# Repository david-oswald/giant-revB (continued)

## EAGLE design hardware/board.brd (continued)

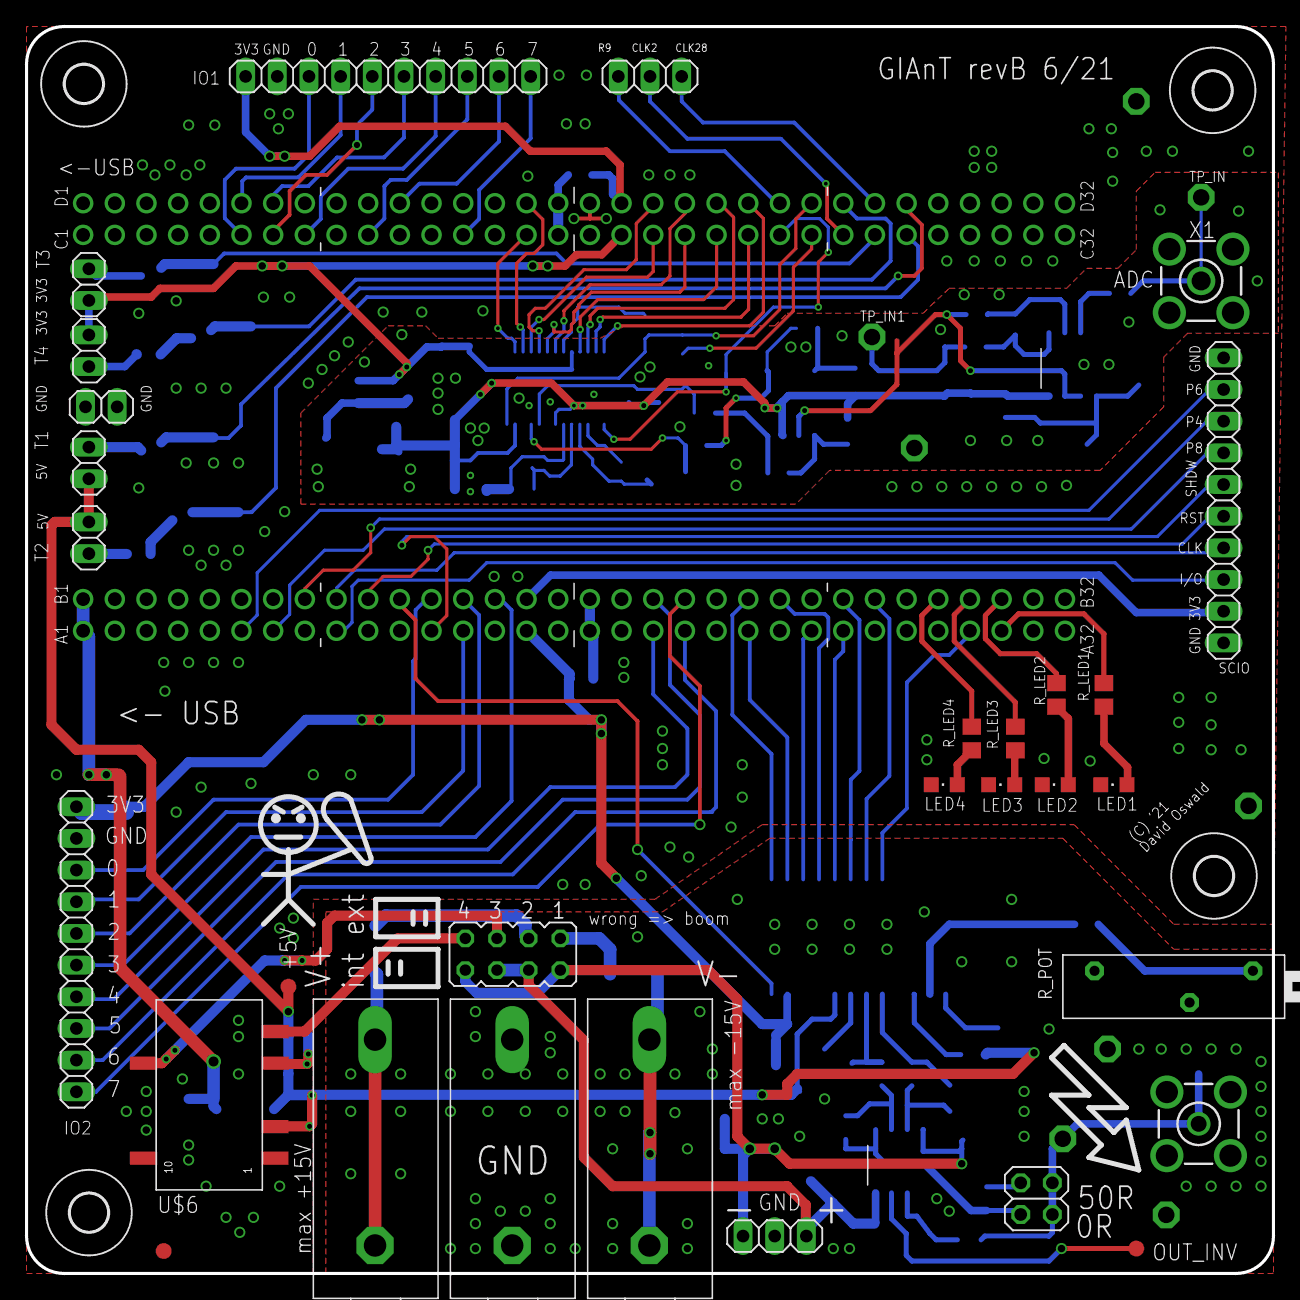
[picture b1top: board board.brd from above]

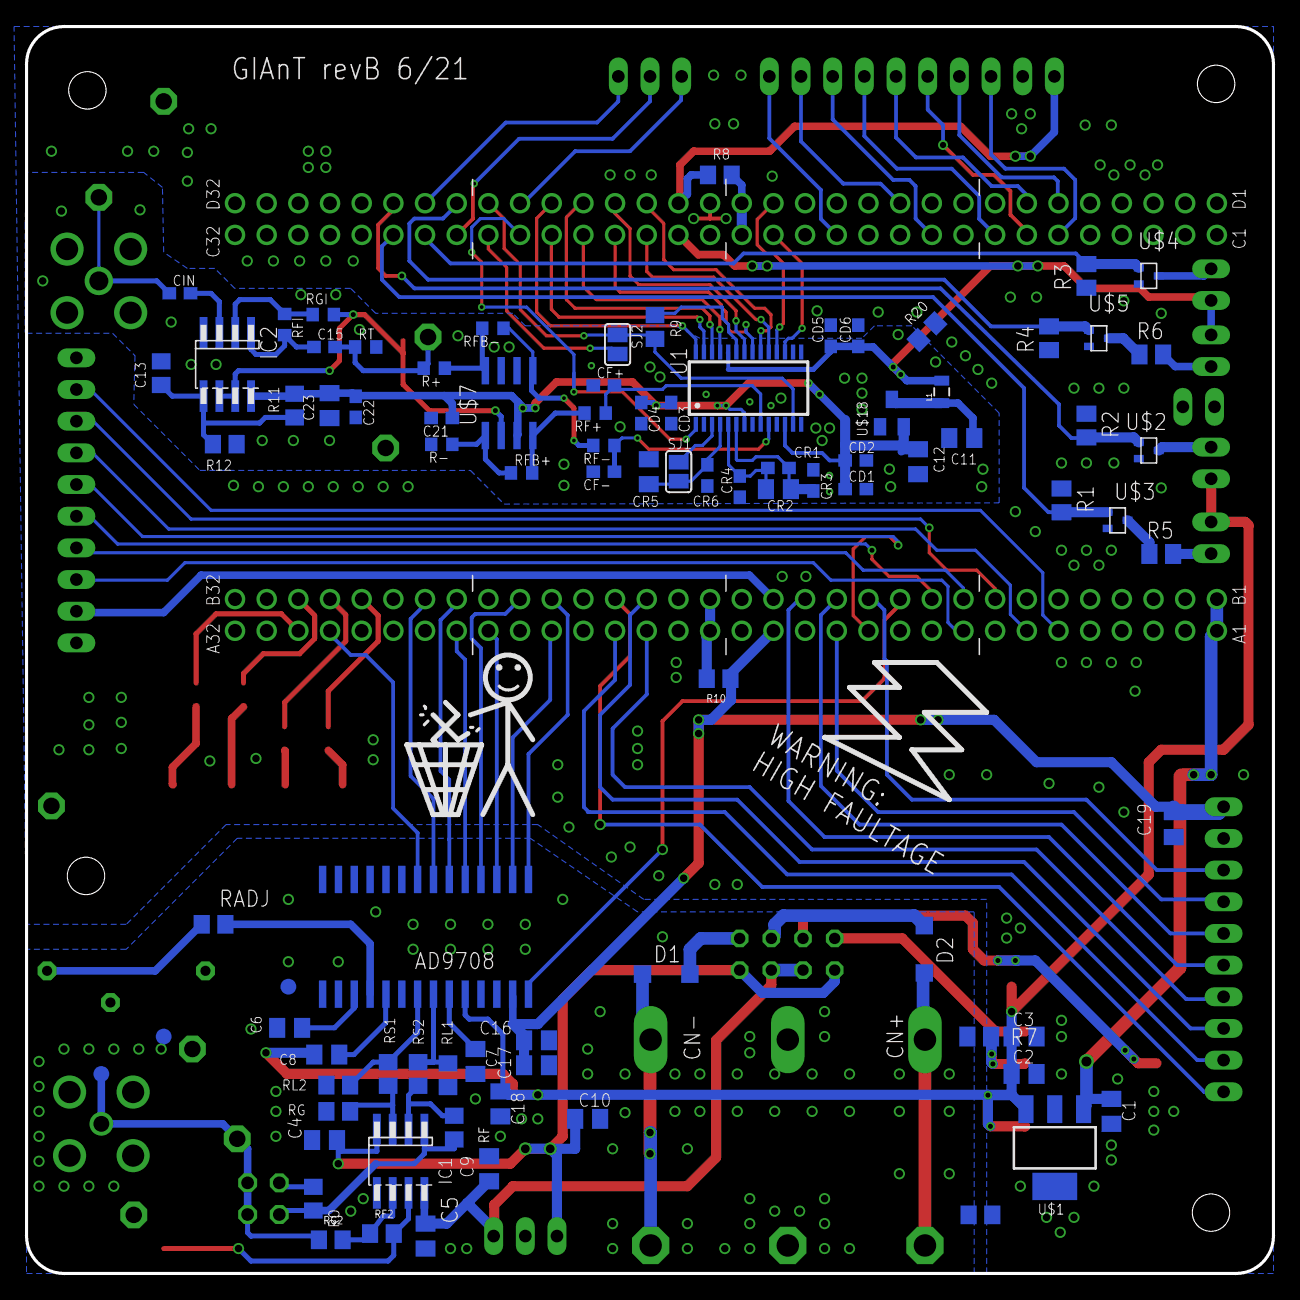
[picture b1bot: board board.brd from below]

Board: 2 copper layers, 100.0 x 100.0 mm, 131 parts (88 on the bottom side), 119 nets.

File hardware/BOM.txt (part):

Qty Value            Device                Package           Parts                                                        Description                            
1                    BU-SMA-V              BU-SMA-V          DAC_OUT                                                      FEMALE SMA CONNECTOR                                      
2                    DIODE-SOD123          SOD123            D1, D2                                                       DIODE                                                                            
4                    DMG1012UW             DMG1012UW1-SMT323 U$2, U$3, U$4, U$5                                           NPN DMG1012UW                                                                    
1                    JP4Q                  JP4Q              JP1                                                          JUMPER                                                                           
4                    LEDCHIPLED_0805       CHIPLED_0805      LED1, LED2, LED3, LED4                                       LED                                                                              
3                    PINHD-1X10            1X10              GPIO, GPIO2, SCIO                                            PIN HEADER                                                                       
5                    PINHD-1X2             1X02              JP2, JP3, JP4, JP5, JP6                                      PIN HEADER                                                                       
2                    PINHD-1X3             1X03              JP7, OP_VCC                                                  PIN HEADER                                                                       
1                    PINHD-2X2             2X02              DAC_T                                                        PIN HEADER                                                                       
4   tbd 	         R-EU_R0805            R0805             R_LED1, R_LED2, R_LED3, R_LED4                               RESISTOR, European symbol                                                        
4   0                R-EU_R0805            R0805             R8, R10, R20, R_GND1                                         RESISTOR, European symbol                                                        
7   0.1u             C-EUC0805K            C0805K            C4, C5, C6, C7, C8, C16, C18                                 CAPACITOR, European symbol                                                       
1   0R               R-EU_M0805            M0805             R7                                                           RESISTOR, European symbol                                                        
2   0R               SJ                    SJ                SJ1, SJ2                                                     SMD solder JUMPER                                                                
1   1.9k             R-EU_R0805            R0805             RADJ                                                         RESISTOR, European symbol                                                        
4   100k             R-EU_M0805            M0805             R1, R2, R3, R4                                               RESISTOR, European symbol                                                        
11  100n             C-EUC0603             C0603             C15, C21, C22, CD1, CD3, CD6, CIN, CR1, CR3, CR4, CR6        CAPACITOR, European symbol                                                       
1   100n             C-EUC0805             C0805             C13                                                          CAPACITOR, European symbol                                                       
1   100n             C-EUC0805K            C0805K            C1                                                           CAPACITOR, European symbol                                                       
1   10k              POTENTIOMETER_PT_SPIN PT-SPIN           R_POT                                                        Potentiometer                                                                    
2   10k              R-EU_R0805            R0805             R11, R12                                                     RESISTOR, European symbol                                                        
3   10n              C-EUC0603             C0603             CD2, CD4, CD5                                                CAPACITOR, European symbol                                                       
1   10n              C-EUC0805K            C0805K            C19                                                          CAPACITOR, European symbol                                                       
5   10u              C-EUC0805K            C0805K            C2, C3, C9, C10, C17                                         CAPACITOR, European symbol                                                       
2   10µ              C-EUC0805K            C0805K            CR2, CR5                                                     CAPACITOR, European symbol                                                       
1   120n, footprint? INDUCTOR0805          0805              L1                                                           Inductors                                                                        
2   1k               R-EU_R0603            R0603             RFB+, RFB-                                                   RESISTOR, European symbol                                                        
2   1µ               C-EUC0805K            C0805K            C11, C12                                                     CAPACITOR, European symbol                                                       
2   20k              R-EU_R0603            R0603             RFI, RGI                                                     RESISTOR, European symbol                                                        
3   24243            24243                 24_243            CN+, CN-, CNG                                                Multicomp 24.243 Series                                                          
1   4.7µ             C-EUC0805K            C0805K            C23                                                          CAPACITOR, European symbol                                                       
3   49               R-EU_R0603            R0603             RF+, RF-, RT                                                 RESISTOR, European symbol                                                        
1   499              R-EU_R0603            R0603             R+                                                           RESISTOR, European symbol                                                        
1   50               R-EU_R0805            R0805             RO                                                           RESISTOR, European symbol                                                        
1   523              R-EU_R0603            R0603             R-                                                           RESISTOR, European symbol                                                        
4   68               R-EU_R0805            R0805             RL1, RL2, RS1, RS2                                           RESISTOR, European symbol                                                        
4   680              R-EU_R0805            R0805             RF, RF2, RG, RG2                                             RESISTOR, European symbol                                                        
1   AD7908           AD7908                SO28W             AD9708                                                       AD9708 8-Bit DAC with current output                                             
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
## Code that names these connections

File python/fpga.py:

# This file contains register definitions and constants for the FPGA
from enum import Enum


class Commands(Enum):
    FPGA_READ_REGISTER = 0x01
    FPGA_WRITE_REGISTER = 0x02
    FPGA_RESET = 0x03

class Registers(Enum):

    ## Read-only registers
    
    # Smartcard
    SC_STATUS = 3
    SC_DATA_OUT = 4
    SC_DATA_OUT_COUNT = 9
    SC_DATA_IN_COUNT = 10

    # PIC programmer
    PIC_DATA_OUT_L = 5
    PIC_DATA_OUT_H = 6
    
    # FI pulse generator
    FI_STATUS = 7
    FI_DATA_OUT = 8
    
    # DDR (currently disabled)
    DDR_DMA_IN_L = 11
    DDR_SINGLE_READ = 17
    DDR_STATUS = 18
    DDR_DMA_IN_H = 19
    
    # Threshold trigger (currently disabled)
    THRESHOLD_STATUS = 12
    
    # Utiming
    UTIMING_STATUS = 13
    
    # UTX
    UTX_PACKET_COUNT = 14
    UTX_STATUS = 22
    
    # URX
    URX_STATUS = 23       
    URX_DATA_OUT = 24  
    URX_PACKET_SIZE_OUT_LOW = 25 
    URX_PACKET_COUNT = 26
    URX_PACKET_SIZE_OUT_HIGH = 29
    
    # Utrig
    UTRIG1_STATUS = 27
    UTRIG2_STATUS = 28
    
    ## Read-write registers
    
    # Smartcard
    SC_CONTROL = 34
    SC_DATA_IN = 35
    
    PIC_CONTROL = 36
    PIC_COMMAND = 37
    PIC_DATA_IN_L = 38
    PIC_DATA_IN_H = 39
    
    # DAC
    DAC_V_LOW = 40
    DAC_V_HIGH = 41
    DAC_V_OFF = 46
    DAC_CONTROL = 48

    # FI pulse generator
    FI_CONTROL = 42
    FI_DATA_IN = 43
    FI_ADDR_L = 44
    FI_ADDR_H = 45
    FI_TRIGGER_CONTROL = 47
    FI_UNIVERSAL_TRIGGER_CONTROL = 81
   
    # Threshold trigger (currently disabled)
    THRESHOLD_CONTROL = 49
    THRESHOLD_VALUE = 61
    
    # Utiming
    UTIMING_CONTROL = 50
    UTIMING_DATA_IN = 51
    UTIMING_ADDR_L = 52
    UTIMING_ADDR_H = 53
    
    # RFID (currently disabled)
    RFID_RESET_TIME = 54
    RFID_CONTROL = 55
    
    # DDR (currently disabled)
    DDR_CONTROL = 56
    DDR_SINGLE_WRITE = 57
    DDR_ADDRESS = 58
    DDR_DATA_COUNT = 59
    
    # Pattern trigger (currently disabled)
    DETECTOR_PATTERN = 60
    DETECTOR_DEBUG = 62
    DETECTOR_PATTERN_SAMPLE_COUNT = 63
    
    # ADC (currently disabled)
    ADC_CONTROL = 64
    
    # Downsampling (currently disabled)
    SCOPE_DOWNSAMPLING_FACTOR = 65
    DETECTOR_DOWNSAMPLING_FACTOR = 66
    
    # UTX
    UTX_CONTROL = 67
    UTX_DATA_IN = 68
    UTX_PACKETSIZE_LO = 69
    UTX_CLKDIV = 70
    UTX_PACKETSIZE_HI = 80
    
    # URX
    URX_CONTROL = 71
    URX_CLKDIV = 72
    URX_DELAY = 73
    
    # Utrig
    UTRIG1_CONTROL = 74
    UTRIG1_DELAY = 75
    UTRIG1_HOLD = 76
    UTRIG2_CONTROL = 77
    UTRIG2_DELAY = 78
    UTRIG2_HOLD = 79
    
    # GPIO switch
    GPIO1_SELECT = 82
    GPIO1_CONTROL = 83
    GPIO_OUTPUTS = 84

class Register_Bits(Enum):
    """register bits definitions"""
    
    # Universal trigger status register bits
    UTRIG_STATUS_ARMED = 0
    UTRIG_STATUS_TRIGGERED = 1

    # Universal trigger control register bits
    UTRIG_CONTROL_ARM = 0
    UTRIG_CONTROL_FORCE = 1
    UTRIG_CONTROL_INPUT_MODE_0 = 2
    UTRIG_CONTROL_INPUT_MODE_1 = 3
    UTRIG_CONTROL_INPUT_MODE_2 = 4
    UTRIG_CONTROL_OUTPUT_MODE_0 = 5
    UTRIG_CONTROL_OUTPUT_MODE_1 = 6
    UTRIG_CONTROL_OUTPUT_MODE_2 = 7

    # Universal TX control register bits
    UTX_CONTROL_START = 0
    UTX_CONTROL_STOP = 1
    UTX_CONTROL_CLEAR = 2
    UTX_CONTROL_OUT_MODE_0 = 3
    UTX_CONTROL_OUT_MODE_1 = 4
    UTX_CONTROL_ONE_TO_Z = 5
    UTX_CONTROL_DISCONNECT_TX_URX = 6
    UTX_CONTROL_ENABLE_UTIMING = 7

    # Universal TX clock control register bits
    UTX_SHIFT_CLK_MODE_0 = 0
    UTX_SHIFT_CLK_MODE_1 = 1

    # UTX status register bits
    UTX_STATUS_READY = 0
    UTX_STATUS_TRANSMITTING = 1

    # Universal RX control register bits
    URX_CONTROL_START = 0
    URX_CONTROL_STOP = 1
    URX_CONTROL_CLEAR = 2
    URX_CONTROL_RESYNC_TO_RISING_EDGES = 3
    URX_CONTROL_RESYNC_TO_FALLING_EDGES = 4
    URX_CONTROL_UTIMING_OR_UTX = 5
    URX_CONTROL_RESYNC_ON_EDGE = 6

    # URX status register bits
    URX_STATUS_READY = 0
    URX_STATUS_RECEIVING = 1
    URX_STATUS_DATA_IN_SAMPLE = 2

    # Universal PW RX control register bits
    URX_PW_CONTROL_START = 0
    URX_PW_CONTROL_STOP = 1
    URX_PW_CONTROL_CLEAR = 2
    URX_PW_CONTROL_RESYNC_TO_RISING_EDGES = 3
    URX_PW_CONTROL_RESYNC_TO_FALLING_EDGES = 4
    URX_PW_CONTROL_UTIMING_OR_UTX = 5
    URX_PW_CONTROL_RESYNC_ON_EDGE = 6

    # URX PW status register bits
    URX_PW_STATUS_READY = 0
    URX_PW_STATUS_RECEIVING = 1
    URX_PW_STATUS_DATA_IN_SAMPLE = 2

    # DDR control register bits
    DDR_CONTROL_WRITE_COMMIT = 0
    DDR_CONTROL_READ_COMMIT = 1
    DDR_CONTROL_SLAVE_FIFO_START = 2
    DDR_CONTROL_RESET = 3
    DDR_CONTROL_DMA_SOFTWARE_WRITE_START = 4
    DDR_CONTROL_DMA_IN_SEL0 = 5
    DDR_CONTROL_DMA_IN_SEL1 = 6

    # DDR status register bits
    DDR_STATUS_DMA = 6

    # Smartcard control register bits
    SC_CONTROL_POWER = 0
    SC_CONTROL_TRANSMIT = 1

    # Smartcard status register bits
    SC_STATUS_POWERED = 0
    SC_STATUS_POWERING_UP = 1
    SC_STATUS_TRANSMITTING = 2
    SC_STATUS_WAITING = 3
    SC_STATUS_DECODING = 4

    # PIC programmer control register bits
    PIC_CONTROL_HAS_DATA = 0
    PIC_CONTROL_GET_RESPONSE = 1
    PIC_CONTROL_TRANSMIT = 2
    PIC_CONTROL_PROG_STARTSTOP = 3
    PIC_CONTROL_START_AND_TRANSMIT = 4

    # DAC control register bits
    DAC_ENABLE = 0
    DAC_TEST_MODE = 1
    DAC_RFID_MODE = 2
    DAC_UTX_MODE = 3

    # ADC control register bits
    ADC_CONTROL_DELAY_INC = 0
    ADC_CONTROL_DELAY_CAL = 1

    # ADC control register bits
    THRESHOLD_CONTROL_ARM = 0
    THRESHOLD_CONTROL_COARSE_TRIGGER_EN = 1
    THRESHOLD_CONTROL_SOFTWARE_TRIGGER = 2
    THRESHOLD_CONTROL_COARSE_TRIGGER_INVERT = 3

    # ADC status register bits
    THRESHOLD_STATUS_ARMED = 0

    # FI control register bits
    FI_CONTROL_W_EN = 0
    FI_CONTROL_ARM = 1
    FI_CONTROL_TRIGGER = 2

    # utiming control register bits
    UTIMING_CONTROL_W_EN = 0
    UTIMING_CONTROL_ARM = 1
    UTIMING_CONTROL_TRIGGER = 2
    UTIMING_CONTROL_DISARM = 3

    # utiming status register bits
    UTIMING_STATUS_READY = 0
    UTIMING_STATUS_ARMED = 1

    # SV control register bits
    SV_CONTROL_VDD = 0
    SV_CONTROL_BUTTON = 1
    SV_CONTROL_SW_TRIGGER_EN = 2
    SV_CONTROL_SW_TRIGGER = 3
    SV_CONTROL_GPIO5 = 7
    SV_CONTROL_GPIO6 = 6

    # FI trigger control register bits
    FI_TRIGGER_CONTROL_DAC_POWER = 0
    FI_TRIGGER_CONTROL_UNIVERSAL = 1
    FI_TRIGGER_CONTROL_EXT1 = 2
    FI_TRIGGER_CONTROL_ADC = 3
    FI_TRIGGER_GPIO_OUTPUT_0 = 4
    FI_TRIGGER_GPIO_OUTPUT_1 = 5
    FI_TRIGGER_CONTROL_INVERT_EDGE = 7
    
    # Universal FI trigger
    FI_UNIVERSAL_TRIGGER_CONTROL_RFID = 0
    FI_UNIVERSAL_TRIGGER_CONTROL_UTX_START = 1
    FI_UNIVERSAL_TRIGGER_CONTROL_UTIMING = 2
    FI_UNIVERSAL_TRIGGER_CONTROL_UTRIG1 = 3
    FI_UNIVERSAL_TRIGGER_CONTROL_SC_SENT = 4
    FI_UNIVERSAL_TRIGGER_CONTROL_SC_START_SEND = 5

    # FI status register bits
    FI_STATUS_READY = 0
    FI_STATUS_ARMED = 1

    # RFID control register bits
    RFID_CONTROL_ENABLED = 0
    RFID_CONTROL_TRIGGER_RESET = 1
    
    # GPIO control bits
    GPIO_ENABLE = 0
    GPIO_CLEAR = 1
    
class GPIO_Pins(Enum):
    GPIO0 = 0
    GPIO1 = 1
    GPIO2 = 2
    GPIO3 = 3
    GPIO4 = 4
    GPIO5 = 5
    GPIO6 = 6
    GPIO7 = 7
    
class GPIO_Select_Bits(Enum):
    UTX_DATA_OUT_VALID = 0
    FI_TRIGGER = 1
    FI_INJECT_FAULT = 2
    UTX_START = 3
    URX_DATA_IN_WITH_TX = 4
    DDR_DMA_START = 5
    SC_DATA_SENDING_TRIGGER = 6
    SC_DATA_SENT_TRIGGER = 7
    THRESH_TRIGGER = 8
    PIC_V_DD_EN = 9
    NOT_PIC_V_PP_EN = 10
    PIC_ISPDAT = 11
    UTIMING_OUT = 12
    UTRIG1_TRIGGER = 13
    UTRIG2_TRIGGER = 14
    GPIO_OUTPUT_0 = 15
    GPIO_OUTPUT_1 = 16
    GPIO_OUTPUT_2 = 17
    GPIO_OUTPUT_3 = 18
    UTX_DATA_OUT = 19
    FI_EXTERNAL_TRIGGER_IN = 20
    VALUE_0 = 29
    VALUE_1 = 30
    VALUE_Z = 31

class FPGA_Vars(Enum):
    # FPGA result codes
    FPGA_SUCCESS = 0x00
    FPGA_FAILURE = 0xff

    # Begin and number of readable/writable registers
    FPGA_REG_READ_BEGIN = 0
    FPGA_REG_WRITE_BEGIN = 32
    FPGA_REG_READ_COUNT = 32+64
    FPGA_REG_WRITE_COUNT = 64

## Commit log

2021-05-26 Initial commit based on https://github.com/janvdherrewegen/bootl-attacks and http://www.sourceforge.net/projects/giant/ and other material
2021-05-27 Working on improved board revB Added DC-DC and selection jumper Added some libraries Fixed THS3062 symbol Split up sheets
2021-05-27 Communication script for LPC bootloader, no faults yet
2021-05-27 Working on glitch example
2021-05-27 Updated FPGA project to latest available ISE 14.7, removed most unused components
2021-05-28 Fixed a bug with wrong sample rate calculations in Python code LPC attack script
2021-05-28 Change DAC controller such that by default it always outputs a zero voltage on reboot etc
2021-05-28 Working on change to new v2 pinout
2021-06-01 Added all v2 pins and labels
2021-06-01 Fully routed (no ADC)
2021-06-02 Porting changes from latest Giant version
2021-06-02 Updated ISE project to pass timing
2021-06-02 Fixed up the GPIO muxes to work, updated test code Fixed various bits around registers and flags inside them Added the current bit file to the repo
2021-06-03 Added internal GPIO pins and trigger function (e.g. for resets)
2021-06-03 Stable params for LPC1343 FI
2021-06-03 Fully routed and freed some space for ADC in middle/right
2021-06-03 Added ADC schematics etc, missing: FPGA pins and routing
2021-06-03 Added ADC pins (unrouted) Moved GCLK pins
2021-06-04 Placed ADC components Changed ADC VR
2021-06-04 Fully routed ADC
2021-06-04 Finalized board, sent to PCBWays
2021-06-07 OS check for detaching kernel USB driver Added short manual to LPC1343 example Updated requirements.txt to include pyserial
2021-06-07 Updated README for Python code Removed old v1 bitstreams Updated stable v2 bitstream
2021-06-09 Updated PDFs and BOM
2021-06-18 UTX clock outputs Added additional internal pins
2021-06-18 Added basic python test for Utx
2021-06-18 Basic UART in TX direction only
2021-06-21 Added (not fully tested) URX Fixed parity in UART and added sendBuffer() function
2021-06-25 Default values for DAC to output a zero voltage
2021-06-25 UART receiving, including Utrigger (not fully complete)
2021-11-17 Board updates Tweaks to LPC First attempt for faultfinder stm32f100
2021-11-17 Updated FPGA code and bitstream to put glitch signal on transistor outputs (non-inverted and inverted)
2021-11-19 Added example for nRF52832
2021-11-19 Renamed glitcher to gl to avoid use before assignment error
2021-11-19 Add note about installing OpenOCD
2021-12-03 Move protection check into a global config "constant".
    Also added more comments and docstrings with descriptions.
2021-12-03 Added nrf52.cfg
2021-12-03 !fixup typo
2021-12-09 Change CRP check to be firmware agnostic.
    Moves away from checking breakpoints, to dumping the image and checking
    whether it's valid.
2021-12-11 Added nRF52832 as an example to the readme
2024-10-22 Added WiP sample for Pi Pico
2024-10-22 Corrected group in udev rules to plugdev
2024-10-23 Fix variances between camelCase and underscore_case, normalise on camelCase
2024-10-23 Adding basic glitch target for Pi Pico
